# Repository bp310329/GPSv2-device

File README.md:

# GPSv2-device
Program of embedded device. This is project of GPS device with sipmle navigation. This device allows for real-time GPS tracking and uploading location data to data base via GSM network, and presentation of this data on the map on website. Second application is simple navigation through points placed on the map.

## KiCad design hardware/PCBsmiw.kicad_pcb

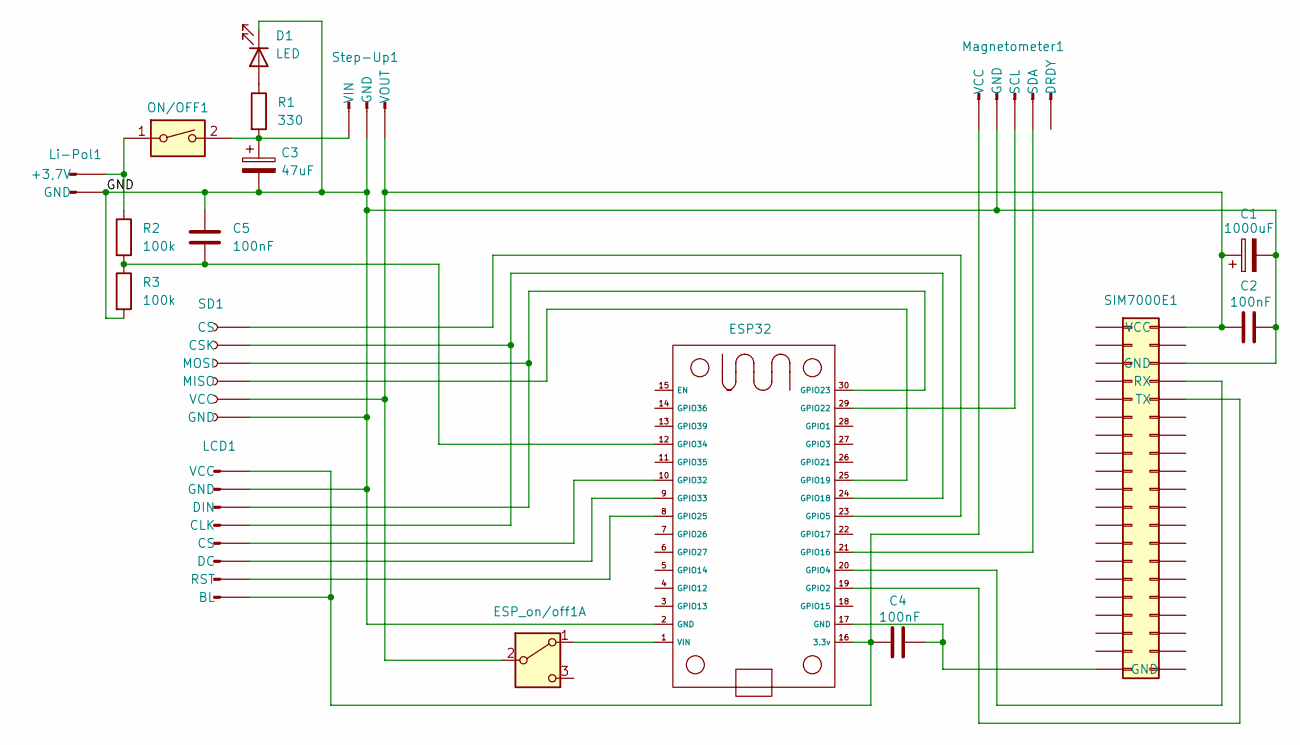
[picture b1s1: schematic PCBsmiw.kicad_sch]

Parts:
C1: 1000uF; CP_Radial_D10.0mm_P5.00mm
C2, C4, C5: 100nF; C_Disc_D3.8mm_W2.6mm_P2.50mm
C3: 47uF; CP_Radial_D5.0mm_P2.00mm
D1: LED; LED_D3.0mm
ESP32: ESP32_30pin
ESP_on/off1: SW_DPDT_x2; SW_CK_JS202011CQN_DPDT_Straight
LCD1: Conn_01x08_Pin; PinSocket_1x08_P2.54mm_Vertical
Li-Pol1: Conn_01x02_Pin; PinHeader_1x02_P2.54mm_Horizontal
Magnetometer1: Conn_01x05_Pin; PinHeader_1x05_P2.54mm_Vertical
ON/OFF1: SW_DIP_x01; SW_DIP_SPSTx01_Slide_9.78x4.72mm_W7.62mm_P2.54mm
R1: 330; R_Axial_DIN0207_L6.3mm_D2.5mm_P7.62mm_Horizontal
R2, R3: 100k; R_Axial_DIN0207_L6.3mm_D2.5mm_P7.62mm_Horizontal
SD1: Conn_01x06_Socket; PinSocket_1x06_P2.54mm_Horizontal
SIM7000E1: Conn_02x20_Odd_Even; PinHeader_2x20_P2.54mm_Vertical
Step-Up1: Conn_01x03_Pin; PinHeader_1x03_P2.54mm_Vertical

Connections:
/GND: C1.2, C2.2, C3.2, C5.1, D1.1 (K), ESP32.2 (GND), LCD1.2 (GND), Li-Pol1.2 (GND), Magnetometer1.2 (GND), R3.2, SD1.6 (GND), SIM7000E1.6 (GND), Step-Up1.2 (GND)
unnamed: C4.2, ESP32.17 (GND), SIM7000E1.39 (GND)
unnamed: D1.2 (A), R1.1
unnamed: C4.1, ESP32.16 (3.3v), LCD1.1 (VCC), LCD1.8 (BL), Magnetometer1.1 (VCC)
unnamed: ESP32.19 (GPIO2), SIM7000E1.10 (TX)
unnamed: ESP32.20 (GPIO4), SIM7000E1.8 (RX)
unnamed: ESP32.23 (GPIO5), SD1.1 (CS)
unnamed: ESP32.21 (GPIO16), Magnetometer1.4 (SDA)
unnamed: ESP32.24 (GPIO18), LCD1.4 (CLK), SD1.2 (CSK)
unnamed: ESP32.25 (GPIO19), SD1.4 (MISO)
unnamed: ESP32.29 (GPIO22), Magnetometer1.3 (SCL)
unnamed: ESP32.30 (GPIO23), LCD1.3 (DIN), SD1.3 (MOSI)
unnamed: ESP32.8 (GPIO25), LCD1.7 (RST)
unnamed: ESP32.10 (GPIO32), LCD1.5 (CS)
unnamed: ESP32.9 (GPIO33), LCD1.6 (DC)
unnamed: C5.2, ESP32.12 (GPIO34), R2.2, R3.1
unnamed: ESP32.1 (VIN), ESP_on/off1.1 (A)
unnamed: C1.1, C2.1, ESP_on/off1.2 (B), SD1.5 (VCC), SIM7000E1.2 (VCC), Step-Up1.1 (VOUT)
unnamed: Li-Pol1.1 (+3,7V), ON/OFF1.1, R2.1
unnamed: C3.1, ON/OFF1.2, R1.2, Step-Up1.3 (VIN)

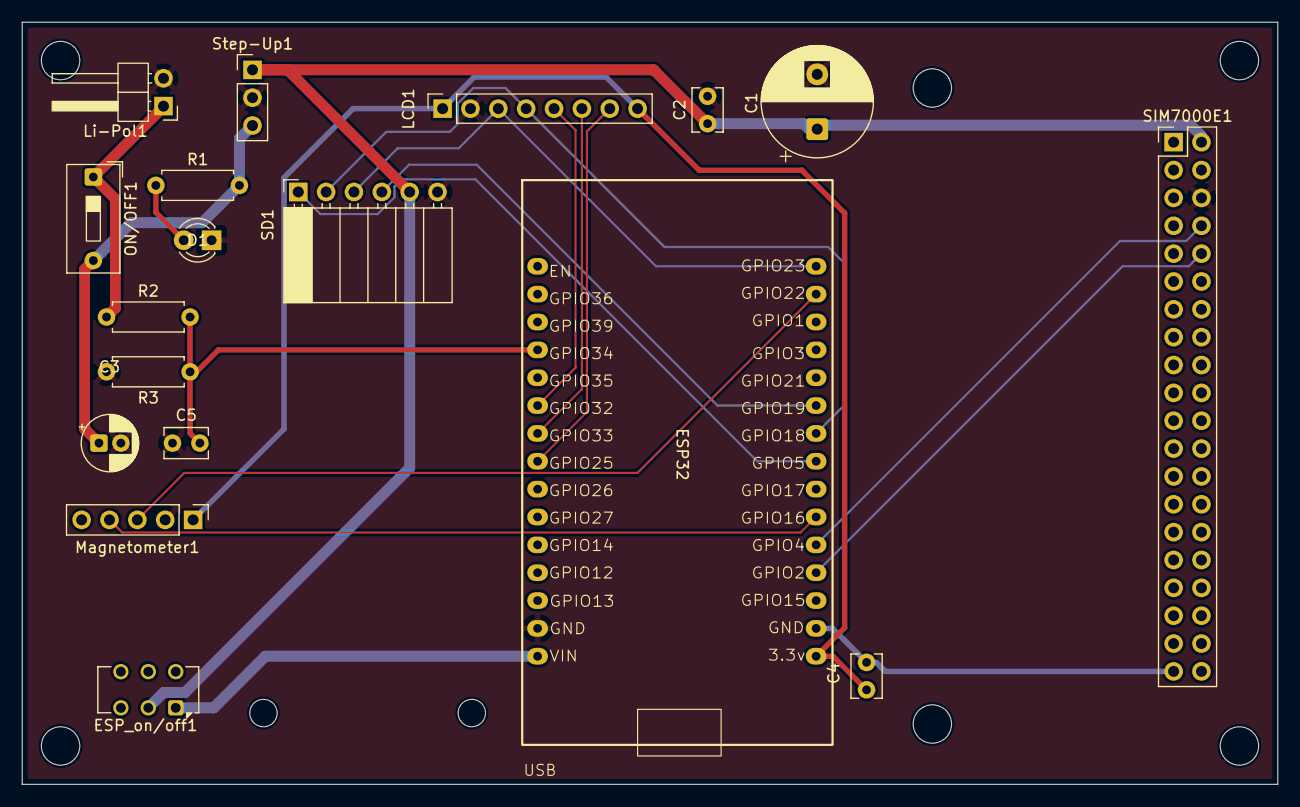
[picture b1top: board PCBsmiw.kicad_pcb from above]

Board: 2 copper layers, 114.5 x 69.5 mm, 18 parts (0 on the bottom side), 20 nets.

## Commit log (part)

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2026-06-18 added SD card handling, multithreading, mode setup, downloading route
2026-06-23 minor fixes
2026-06-24 finished project
